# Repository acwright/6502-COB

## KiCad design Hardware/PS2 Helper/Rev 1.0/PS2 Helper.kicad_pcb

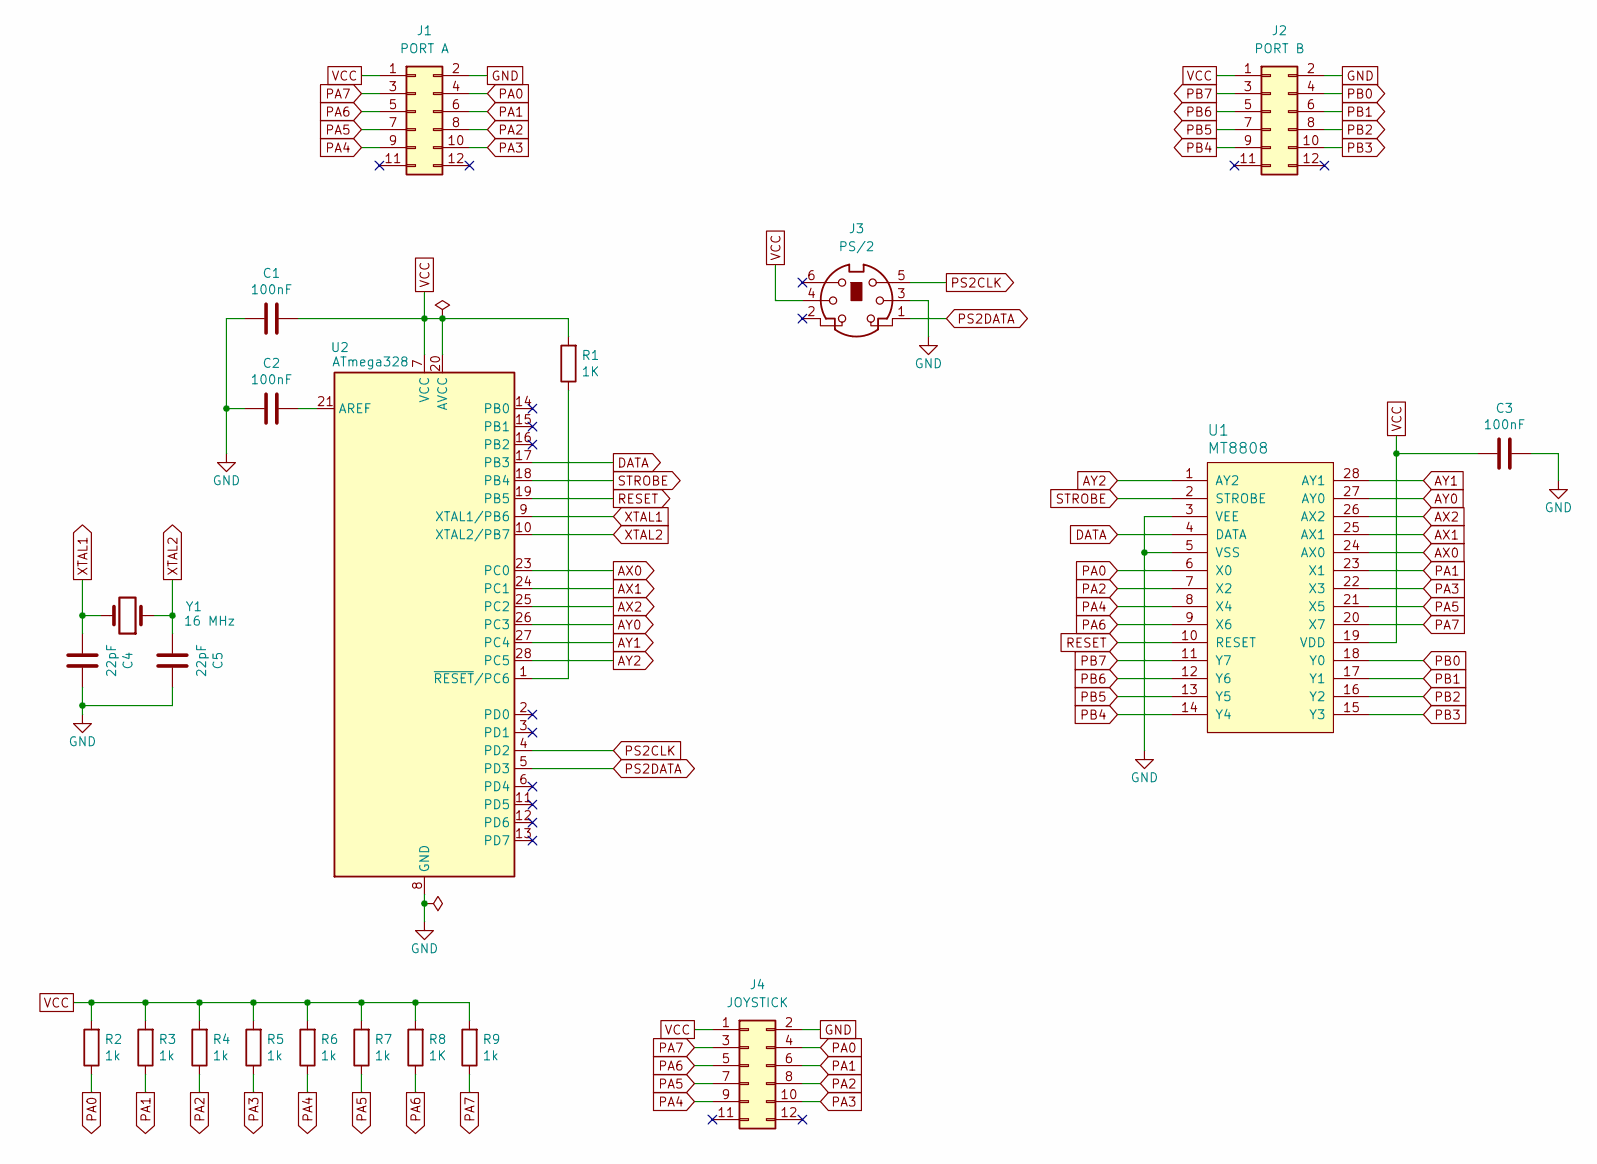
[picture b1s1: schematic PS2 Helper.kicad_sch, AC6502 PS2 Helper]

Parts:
C1, C2, C3: 100nF; C_Disc_D5.0mm_W2.5mm_P2.50mm; Digikey 478-3187-ND
C4, C5: 22pF; C_Disc_D5.0mm_W2.5mm_P2.50mm; Digikey 478-4846-ND
J1: PORT A; 6502 GPIO Connector; Digikey 2057-BHR-12-VUA-ND
J2: PORT B; 6502 GPIO Connector; Digikey 2057-BHR-12-VUA-ND
J3: PS/2; PS2 Jack; Digikey 2092-KMDGX-6S-BS-ND
J4: JOYSTICK; 6502 GPIO Connector; Digikey 2057-BHR-12-VUA-ND
R1, R8: 1K; R_Axial_DIN0204_L3.6mm_D1.6mm_P5.08mm_Horizontal; Digikey 13-MFR-12FTF52-1KCT-ND
R2, R3, R4, R5, R6, R7, R9: 1k; R_Axial_DIN0204_L3.6mm_D1.6mm_P5.08mm_Horizontal; Digikey 13-MFR-12FTF52-1KCT-ND
U1: MT8808; DIP-28_W15.24mm_Socket_LongPads
U2: ATmega328; DIP-28_W7.62mm_Socket_LongPads; Digikey ATMEGA328P-PU-ND
Y1: 16 MHz; Crystal_HC49-U_Vertical; Digikey X1103-ND

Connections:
AX0: U1.24 (AX0), U2.23 (PC0)
AX1: U1.25 (AX1), U2.24 (PC1)
AX2: U1.26 (AX2), U2.25 (PC2)
AY0: U1.27 (AY0), U2.26 (PC3)
AY1: U1.28 (AY1), U2.27 (PC4)
AY2: U1.1 (AY2), U2.28 (PC5)
DATA: U1.4 (DATA), U2.17 (PB3)
GND: C1.1, C2.1, C3.2, C4.2, C5.2, J1.2, J2.2, J3.3, J4.2, U1.3 (VEE), U1.5 (VSS), U2.8 (GND), U2.22 (GND)
unnamed: C2.2, U2.21 (AREF)
unnamed: R1.1, U2.1 (~RESET/PC6)
PA0: J1.4, J4.4, R2.1, U1.6 (X0)
PA1: J1.6, J4.6, R3.1, U1.23 (X1)
PA2: J1.8, J4.8, R4.1, U1.7 (X2)
PA3: J1.10, J4.10, R5.1, U1.22 (X3)
PA4: J1.9, J4.9, R6.1, U1.8 (X4)
PA5: J1.7, J4.7, R7.1, U1.21 (X5)
PA6: J1.5, J4.5, R8.1, U1.9 (X6)
PA7: J1.3, J4.3, R9.1, U1.20 (X7)
PB0: J2.4, U1.18 (Y0)
PB1: J2.6, U1.17 (Y1)
PB2: J2.8, U1.16 (Y2)
PB3: J2.10, U1.15 (Y3)
PB4: J2.9, U1.14 (Y4)
PB5: J2.7, U1.13 (Y5)
PB6: J2.5, U1.12 (Y6)
PB7: J2.3, U1.11 (Y7)
PS2CLK: J3.5, U2.4 (PD2)
PS2DATA: J3.1, U2.5 (PD3)
RESET: U1.10 (RESET), U2.19 (PB5)
STROBE: U1.2 (STROBE), U2.18 (PB4)
VCC: C1.2, C3.1, J1.1, J2.1, J3.4, J4.1, R1.2, R2.2, R3.2, R4.2, R5.2, R6.2, R7.2, R8.2, R9.2, U1.19 (VDD), U2.7 (VCC), U2.20 (AVCC)
XTAL1: C4.1, U2.9 (XTAL1/PB6), Y1.2
XTAL2: C5.1, U2.10 (XTAL2/PB7), Y1.1

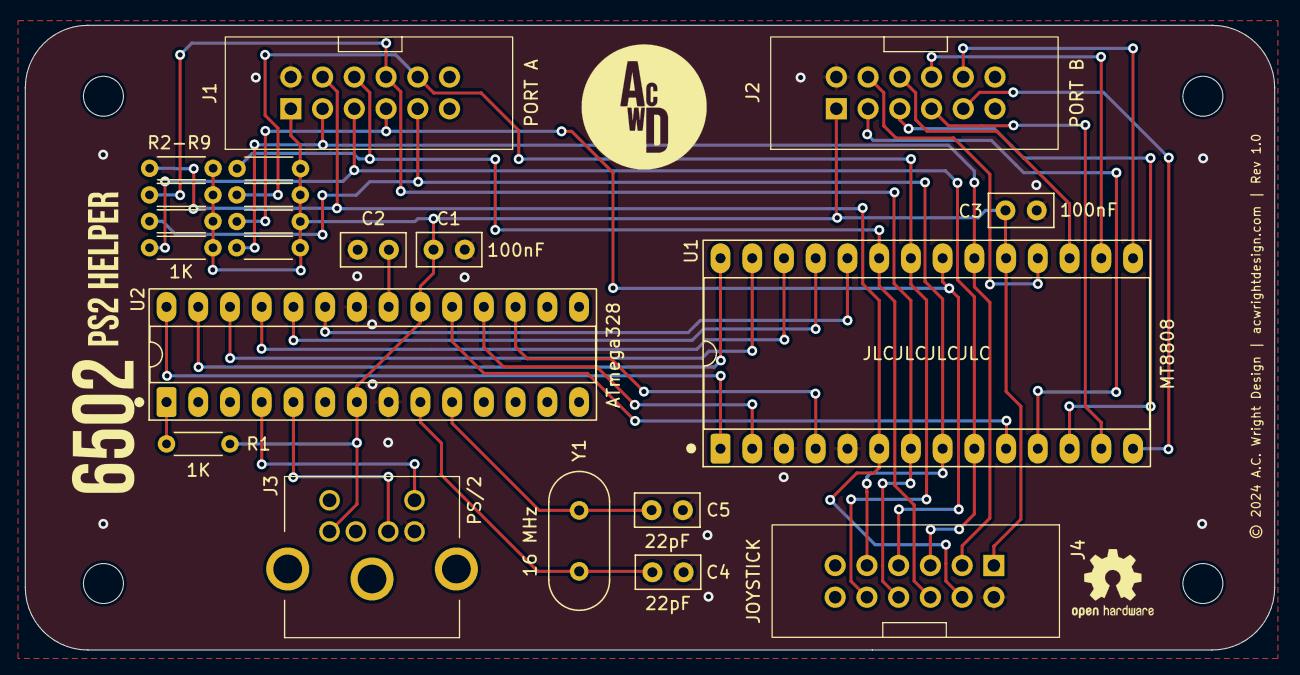
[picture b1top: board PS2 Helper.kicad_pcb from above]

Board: 2 copper layers, 100.0 x 50.0 mm, 25 parts (0 on the bottom side), 33 nets.

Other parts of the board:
H1, H2, H3, H4: MountingHole; MountingHole_3.2mm_M3

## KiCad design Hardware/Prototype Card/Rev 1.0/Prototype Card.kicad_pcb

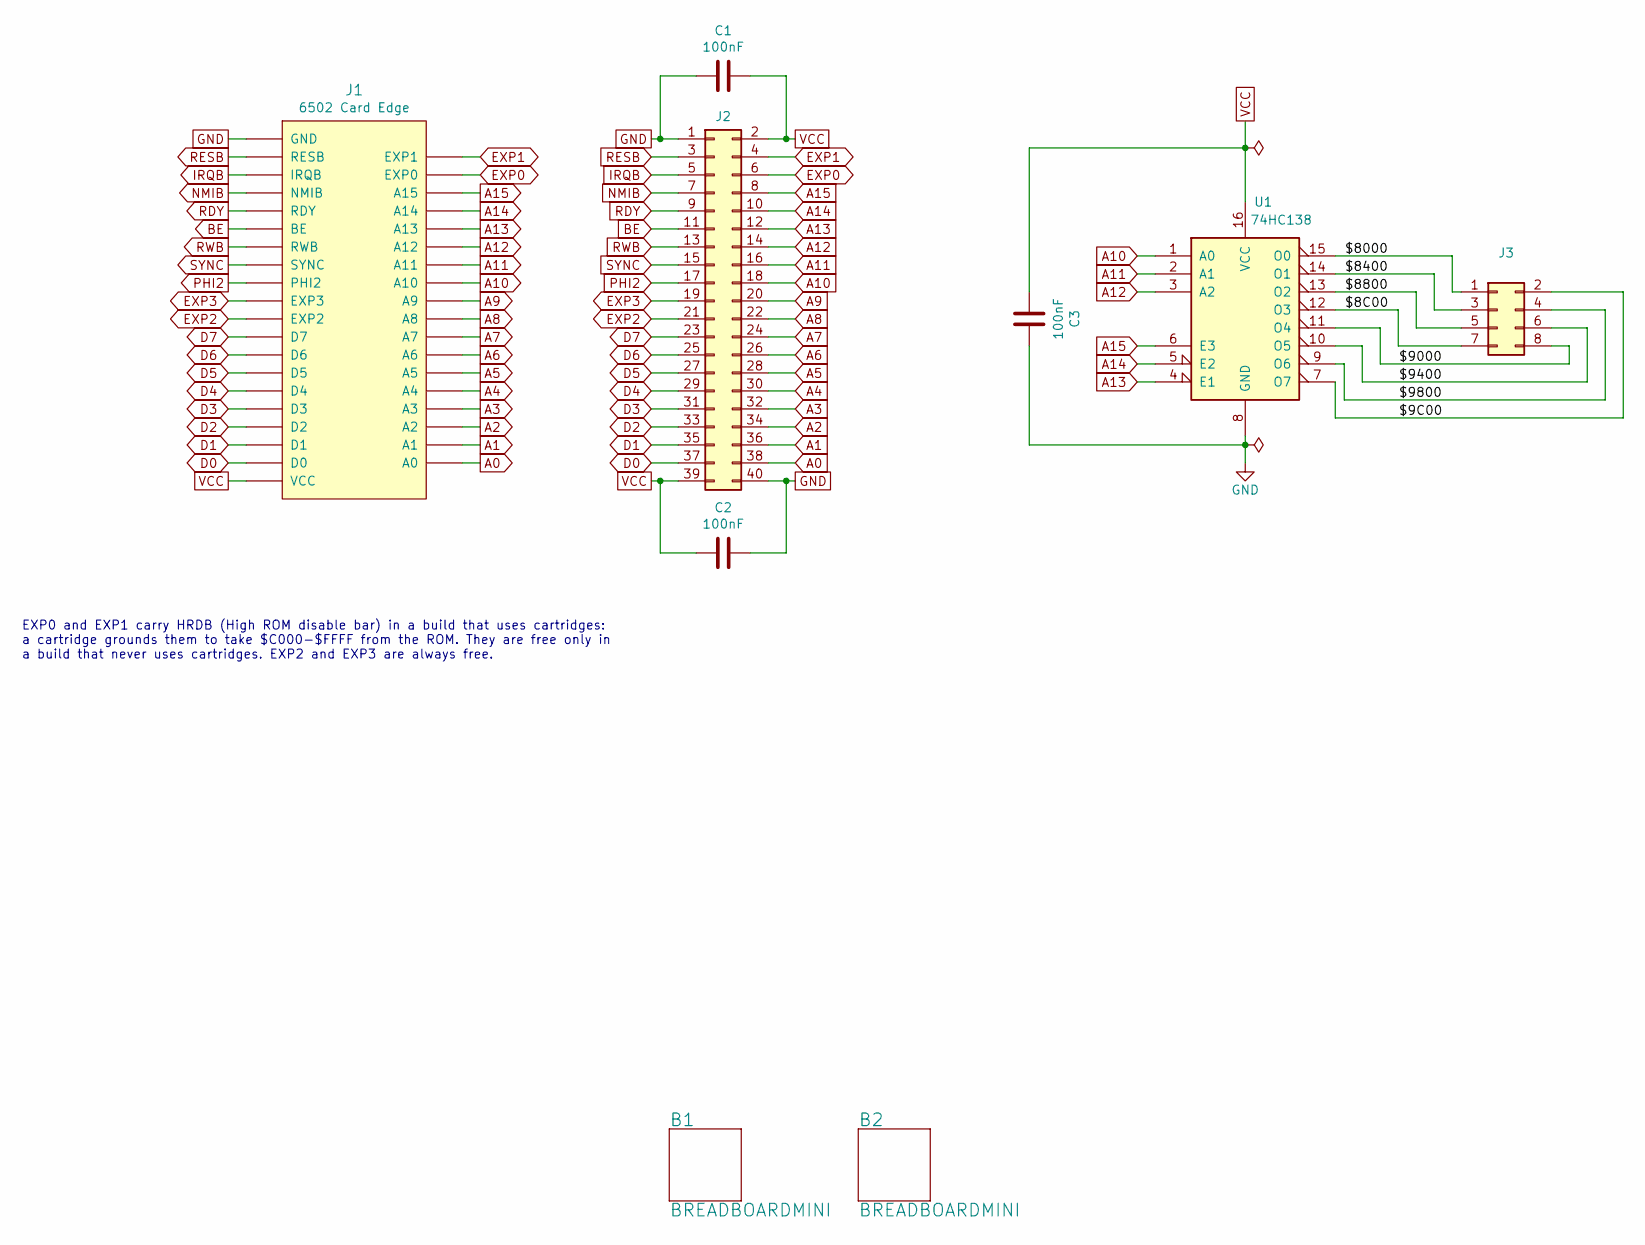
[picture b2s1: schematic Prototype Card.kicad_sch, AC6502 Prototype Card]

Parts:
B1, B2: BREADBOARDMINI; Breadboard Mini; Mouser 474-PRT-12047
C1, C2, C3: 100nF; C_0805_2012Metric; LCSC C49678
J1: 6502 Card Edge
J2: 6502 Bus; PinSocket_2x20_P2.54mm_Vertical; Digikey S7123-ND
J3: Conn_02x04_Odd_Even; PinHeader_2x04_P2.54mm_Vertical; Digikey S2011EC-40-ND
U1: 74HC138; SOIC-16_3.9x9.9mm_P1.27mm; LCSC C5602

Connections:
/$8C00: J3.7, U1.12 (O3)
/$9C00: J3.2, U1.7 (O7)
/$8000: J3.1, U1.15 (O0)
/$8400: J3.3, U1.14 (O1)
/$8800: J3.5, U1.13 (O2)
/$9000: J3.8, U1.11 (O4)
/$9400: J3.6, U1.10 (O5)
/$9800: J3.4, U1.9 (O6)
A0: J1.A0, J2.38
A1: J1.A1, J2.36
A2: J1.A2, J2.34
A3: J1.A3, J2.32
A4: J1.A4, J2.30
A5: J1.A5, J2.28
A6: J1.A6, J2.26
A7: J1.A7, J2.24
A8: J1.A8, J2.22
A9: J1.A9, J2.20
A10: J1.A10, J2.18, U1.1 (A0)
A11: J1.A11, J2.16, U1.2 (A1)
A12: J1.A12, J2.14, U1.3 (A2)
A13: J1.A13, J2.12, U1.4 (E1)
A14: J1.A14, J2.10, U1.5 (E2)
A15: J1.A15, J2.8, U1.6 (E3)
BE: J1.BE, J2.11
D0: J1.D0, J2.37
D1: J1.D1, J2.35
D2: J1.D2, J2.33
D3: J1.D3, J2.31
D4: J1.D4, J2.29
D5: J1.D5, J2.27
D6: J1.D6, J2.25
D7: J1.D7, J2.23
EXP0: J1.EXP0, J2.6
EXP1: J1.EXP1, J2.4
EXP2: J1.EXP2, J2.21
EXP3: J1.EXP3, J2.19
GND: C1.1, C2.2, C3.2, J1.GND, J2.1, J2.40, U1.8 (GND)
IRQB: J1.IRQB, J2.5
NMIB: J1.NMIB, J2.7
PHI2: J1.PHI2, J2.17
RDY: J1.RDY, J2.9
RESB: J1.RESB, J2.3
RWB: J1.RWB, J2.13
SYNC: J1.SYNC, J2.15
VCC: C1.2, C2.1, C3.1, J1.VCC, J2.2, J2.39, U1.16 (VCC)

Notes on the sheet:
EXP0 and EXP1 carry HRDB (High ROM disable bar) in a build that uses cartridges: a cartridge grounds them to take $C000-$FFFF from the ROM. They are free only in a build that never uses cartridges. EXP2 and EXP3 are always free.

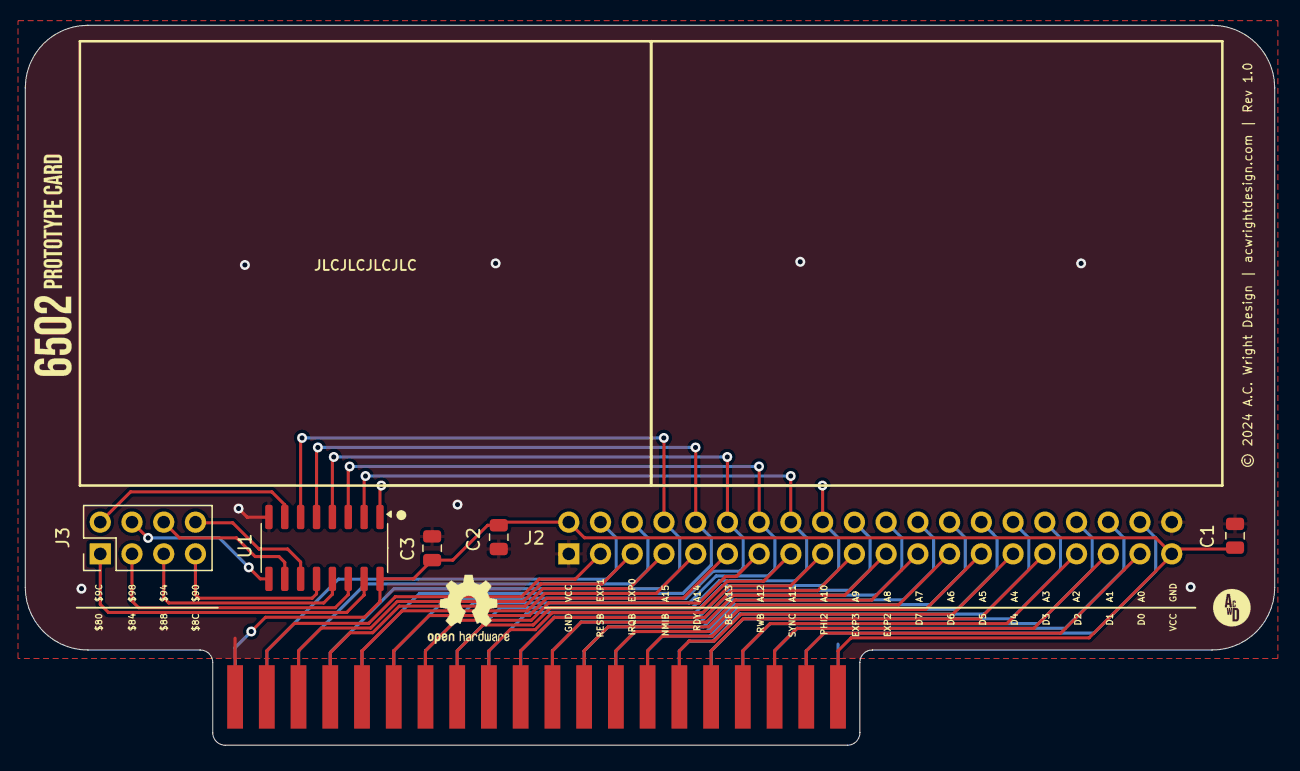
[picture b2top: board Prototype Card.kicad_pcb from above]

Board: 2 copper layers, 100.0 x 57.6 mm, 9 parts (1 on the bottom side), 46 nets.

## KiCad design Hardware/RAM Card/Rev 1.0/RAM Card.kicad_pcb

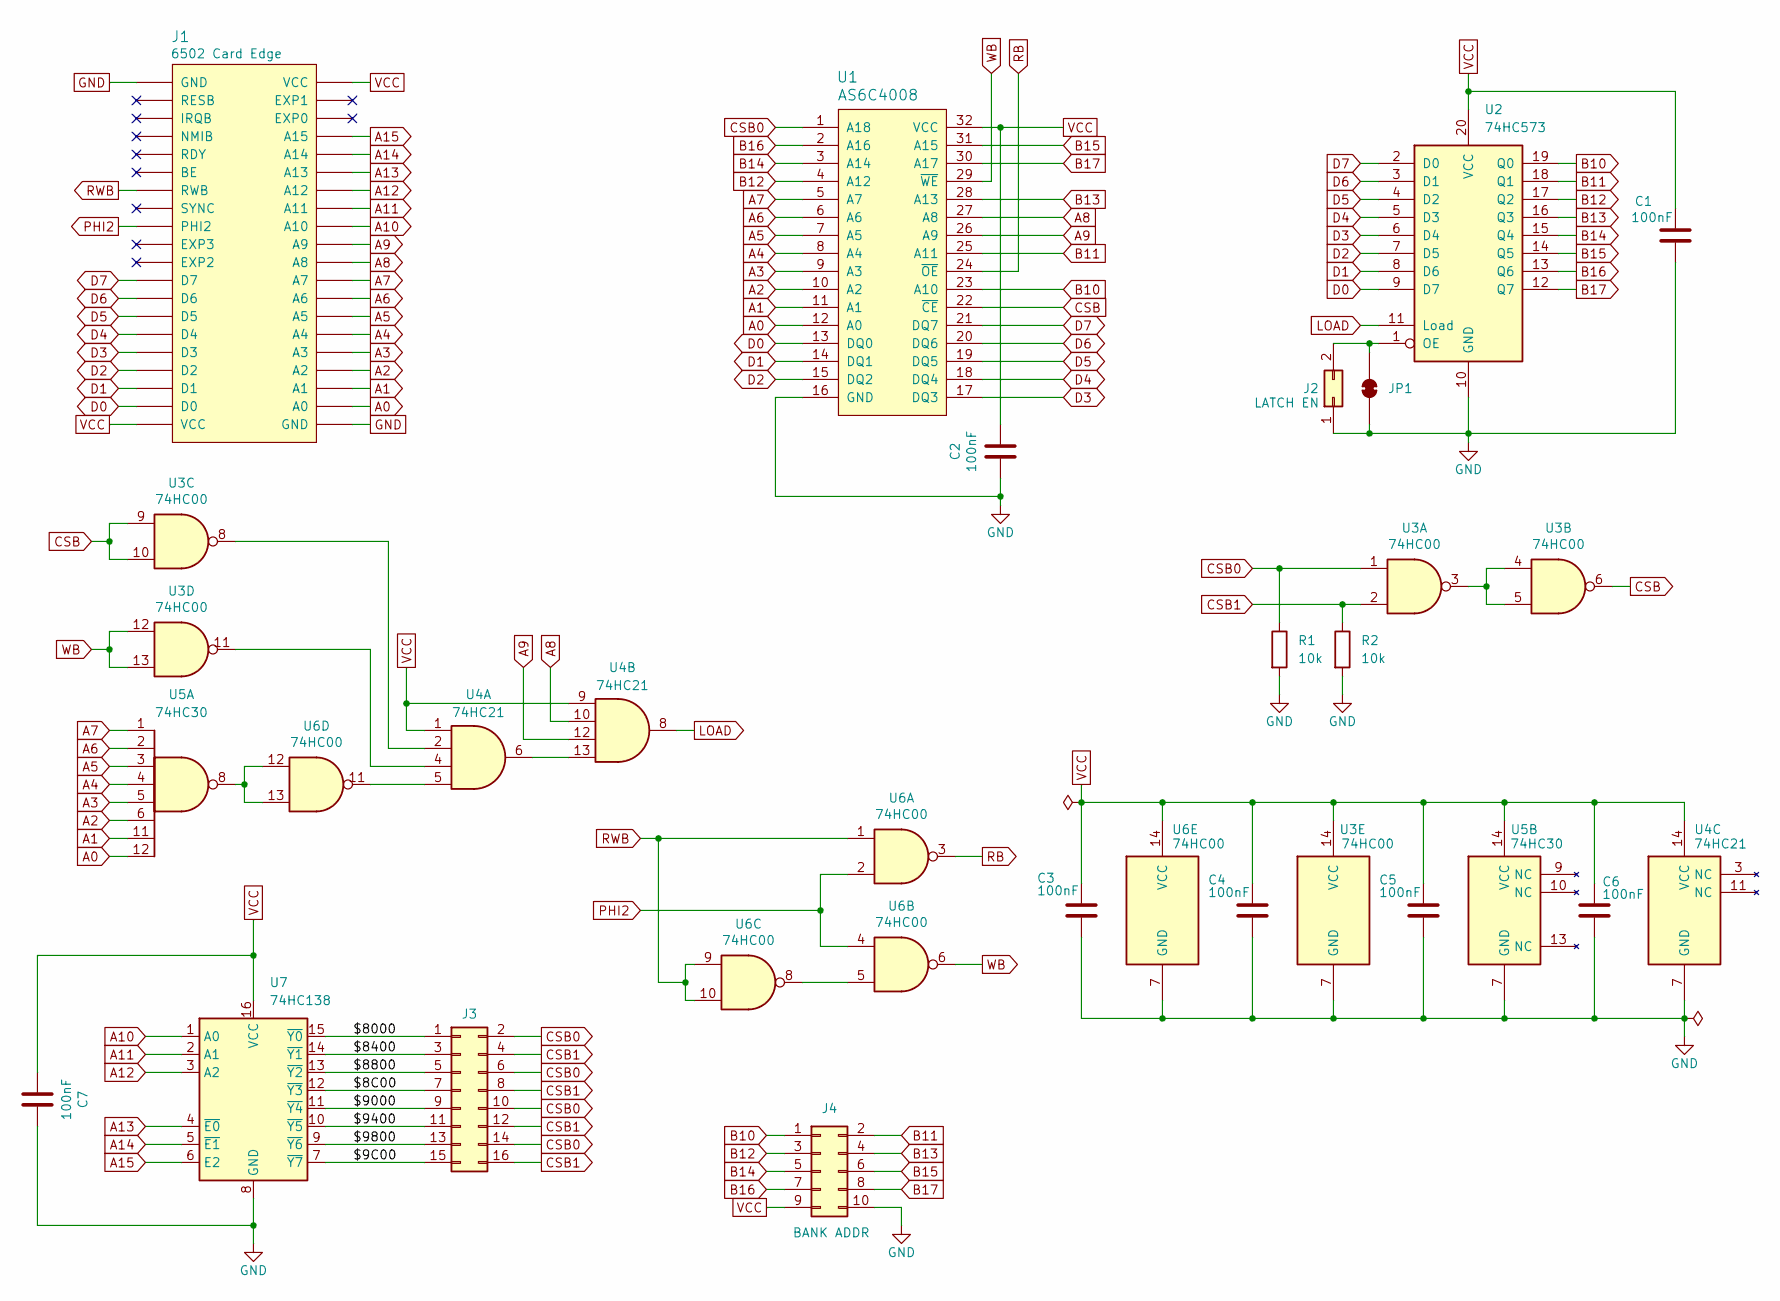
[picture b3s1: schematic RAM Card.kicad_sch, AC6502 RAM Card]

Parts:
C1, C2, C3, C4, C5, C6, C7: 100nF; C_0805_2012Metric; LCSC C49678
J1: 6502 Card Edge
J2: LATCH EN; PinHeader_1x02_P2.54mm_Vertical; Digikey S1011EC-40-ND
J3: Conn_02x08_Odd_Even; PinHeader_2x08_P2.54mm_Vertical; Digikey S2011EC-40-ND
J4: BANK ADDR; PinHeader_2x05_P2.54mm_Vertical; Digikey S2011EC-40-ND
JP1: Latch Enable; SolderJumper-2_P1.3mm_Bridged_RoundedPad1.0x1.5mm
R1, R2: 10k; R_0805_2012Metric; LCSC C17414
U1: AS6C4008; DIP-32_W15.24mm_Socket_LongPads; Digikey 1450-1027-ND
U2: 74HC573; SOIC-20W_7.5x12.8mm_P1.27mm; LCSC C5608
U3, U6: 74HC00; SOIC-14_3.9x8.7mm_P1.27mm; LCSC C5586
U4: 74HC21; SOIC-14_3.9x8.7mm_P1.27mm; LCSC C75398
U5: 74HC30; SOIC-14_3.9x8.7mm_P1.27mm; LCSC C19818870
U7: 74HC138; SOIC-16_3.9x9.9mm_P1.27mm; LCSC C5602

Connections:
/$8C00: J3.7, U7.12 (~Y3)
/$9C00: J3.15, U7.7 (~Y7)
/$8000: J3.1, U7.15 (~Y0)
/$8400: J3.3, U7.14 (~Y1)
/$8800: J3.5, U7.13 (~Y2)
/$9000: J3.9, U7.11 (~Y4)
/$9400: J3.11, U7.10 (~Y5)
/$9800: J3.13, U7.9 (~Y6)
A0: J1.A0, U1.12 (A0), U5.12
A1: J1.A1, U1.11 (A1), U5.11
A2: J1.A2, U1.10 (A2), U5.6
A3: J1.A3, U1.9 (A3), U5.5
A4: J1.A4, U1.8 (A4), U5.4
A5: J1.A5, U1.7 (A5), U5.3
A6: J1.A6, U1.6 (A6), U5.2
A7: J1.A7, U1.5 (A7), U5.1
A8: J1.A8, U1.27 (A8), U4.10
A9: J1.A9, U1.26 (A9), U4.12
A10: J1.A10, U7.1 (A0)
A11: J1.A11, U7.2 (A1)
A12: J1.A12, U7.3 (A2)
A13: J1.A13, U7.4 (~E0)
A14: J1.A14, U7.5 (~E1)
A15: J1.A15, U7.6 (E2)
B10: J4.1, U1.23 (A10), U2.19 (Q0)
B11: J4.2, U1.25 (A11), U2.18 (Q1)
B12: J4.3, U1.4 (A12), U2.17 (Q2)
B13: J4.4, U1.28 (A13), U2.16 (Q3)
B14: J4.5, U1.3 (A14), U2.15 (Q4)
B15: J4.6, U1.31 (A15), U2.14 (Q5)
B16: J4.7, U1.2 (A16), U2.13 (Q6)
B17: J4.8, U1.30 (A17), U2.12 (Q7)
CSB: U1.22 (~CE), U3.6, U3.9, U3.10
CSB0: J3.2, J3.6, J3.10, J3.14, R1.1, U1.1 (A18), U3.1
CSB1: J3.4, J3.8, J3.12, J3.16, R2.1, U3.2
D0: J1.D0, U1.13 (DQ0), U2.9 (D7)
D1: J1.D1, U1.14 (DQ1), U2.8 (D6)
D2: J1.D2, U1.15 (DQ2), U2.7 (D5)
D3: J1.D3, U1.17 (DQ3), U2.6 (D4)
D4: J1.D4, U1.18 (DQ4), U2.5 (D3)
D5: J1.D5, U1.19 (DQ5), U2.4 (D2)
D6: J1.D6, U1.20 (DQ6), U2.3 (D1)
D7: J1.D7, U1.21 (DQ7), U2.2 (D0)
GND: C1.2, C2.2, C3.2, C4.2, C5.2, C6.2, C7.2, J1.GND, J2.1, J4.10, JP1.1 (A), R1.2, R2.2, U1.16 (GND), U2.10 (GND), U3.7 (GND), U4.7 (GND), U5.7 (GND), U6.7 (GND), U7.8 (GND)
LOAD: U2.11 (Load), U4.8
unnamed: J2.2, JP1.2 (B), U2.1 (OE)
unnamed: U3.3, U3.4, U3.5
unnamed: U3.8, U4.2
unnamed: U3.11, U4.4
unnamed: U4.5, U6.11
unnamed: U4.6, U4.13
unnamed: U5.8, U6.12, U6.13
unnamed: U6.5, U6.8
PHI2: J1.PHI2, U6.2, U6.4
RB: U1.24 (~OE), U6.3
RWB: J1.RWB, U6.1, U6.9, U6.10
VCC: C1.1, C2.1, C3.1, C4.1, C5.1, C6.1, C7.1, J1.VCC, J4.9, U1.32 (VCC), U2.20 (VCC), U3.14 (VCC), U4.1, U4.9, U4.14 (VCC), U5.14 (VCC), U6.14 (VCC), U7.16 (VCC)
WB: U1.29 (~WE), U3.12, U3.13, U6.6

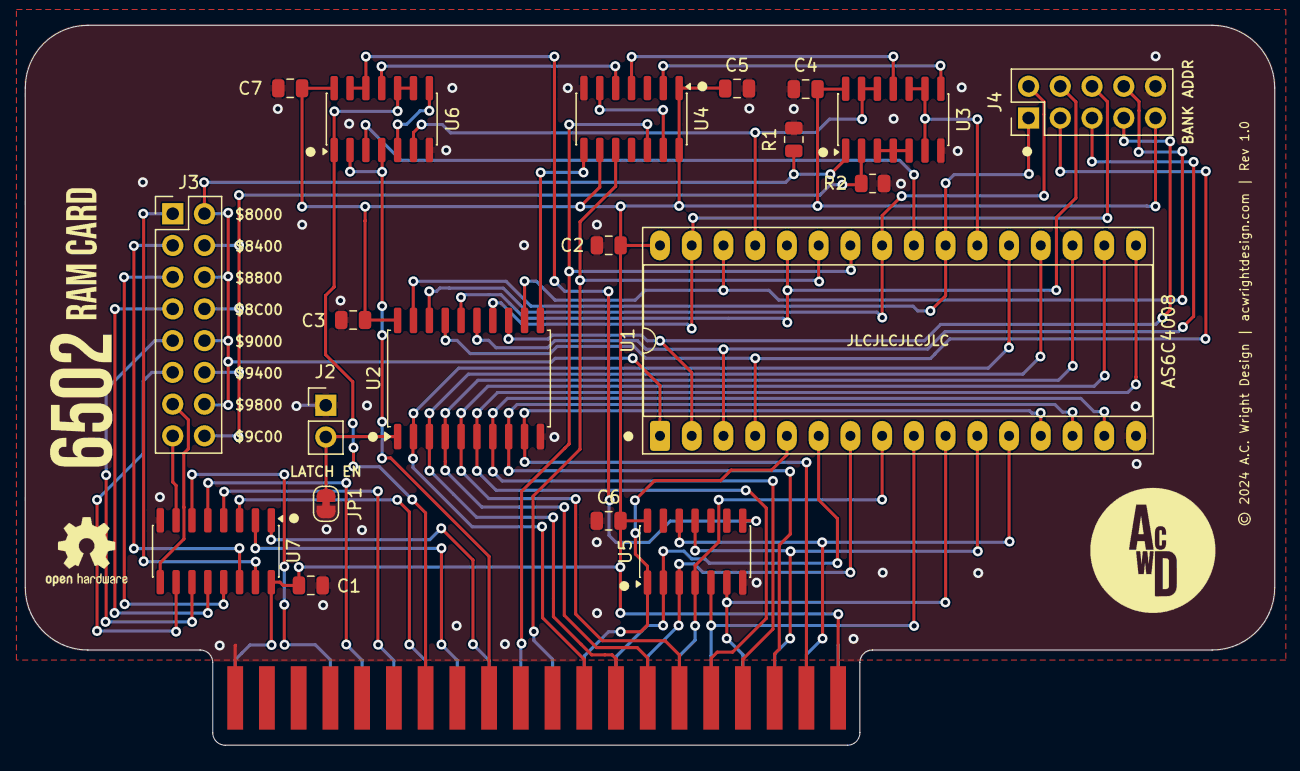
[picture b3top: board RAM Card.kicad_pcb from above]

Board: 2 copper layers, 100.0 x 57.6 mm, 21 parts (0 on the bottom side), 58 nets.

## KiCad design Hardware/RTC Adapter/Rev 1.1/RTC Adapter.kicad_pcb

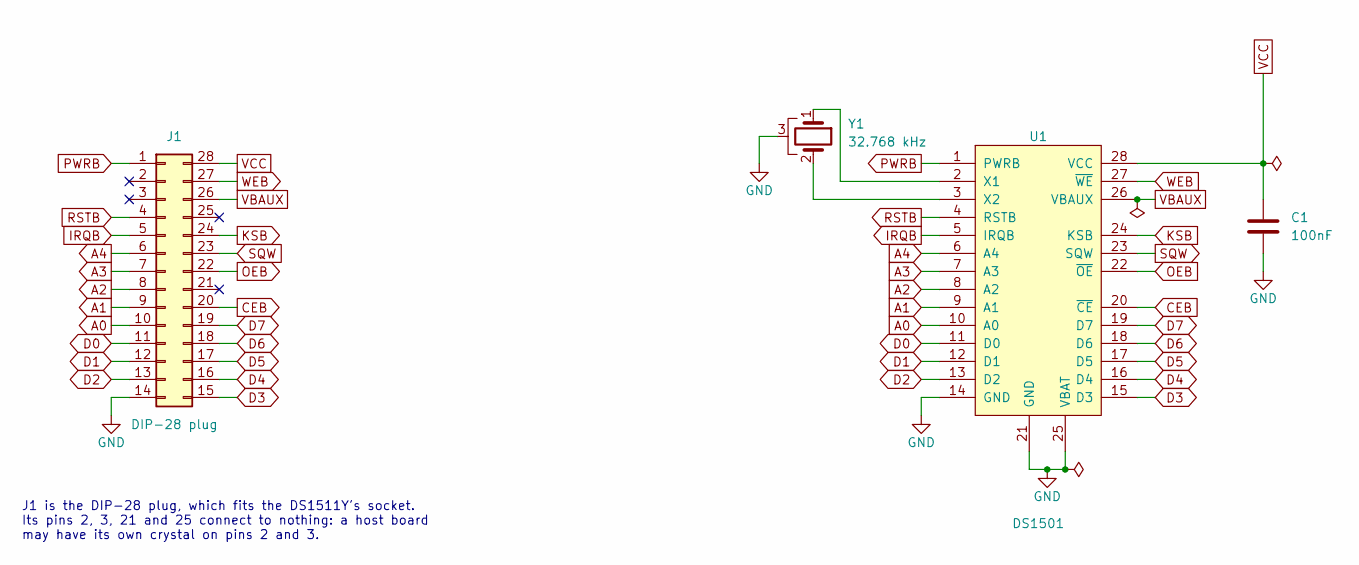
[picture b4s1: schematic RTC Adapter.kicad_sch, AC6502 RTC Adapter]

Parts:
C1: 100nF; C_Disc_D5.0mm_W2.5mm_P2.50mm; Digikey 478-3187-ND
J1: DIP-28 plug; DIP-28 Plug; Digikey ED7264-64-ND
U1: DS1501; SOIC-28W_7.5x17.9mm_P1.27mm; Digikey DS1501YZN+-ND
Y1: 32.768 kHz; Crystal_C26-LF_D2.1mm_L6.5mm_Horizontal_1EP_style1; Digikey 535-AB26T-32.768KHZ-6CT-ND

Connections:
A0: J1.10, U1.10 (A0)
A1: J1.9, U1.9 (A1)
A2: J1.8, U1.8 (A2)
A3: J1.7, U1.7 (A3)
A4: J1.6, U1.6 (A4)
CEB: J1.20, U1.20 (~CE)
D0: J1.11, U1.11 (D0)
D1: J1.12, U1.12 (D1)
D2: J1.13, U1.13 (D2)
D3: J1.15, U1.15 (D3)
D4: J1.16, U1.16 (D4)
D5: J1.17, U1.17 (D5)
D6: J1.18, U1.18 (D6)
D7: J1.19, U1.19 (D7)
GND: C1.2, J1.14, U1.14 (GND), U1.21 (GND), U1.25 (VBAT), Y1.3
IRQB: J1.5, U1.5 (IRQB)
KSB: J1.24, U1.24 (KSB)
unnamed: U1.2 (X1), Y1.1
unnamed: U1.3 (X2), Y1.2
OEB: J1.22, U1.22 (~OE)
PWRB: J1.1, U1.1 (PWRB)
RSTB: J1.4, U1.4 (RSTB)
SQW: J1.23, U1.23 (SQW)
VBAUX: J1.26, U1.26 (VBAUX)
VCC: C1.1, J1.28, U1.28 (VCC)
WEB: J1.27, U1.27 (~WE)

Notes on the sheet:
J1 is the DIP-28 plug, which fits the DS1511Y's socket. Its pins 2, 3, 21 and 25 connect to nothing: a host board may have its own crystal on pins 2 and 3.

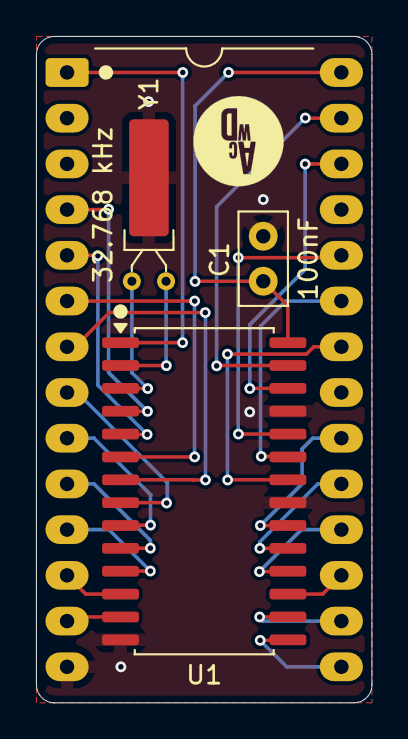
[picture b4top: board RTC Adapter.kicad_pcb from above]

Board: 2 copper layers, 18.6 x 37.0 mm, 4 parts (0 on the bottom side), 26 nets.

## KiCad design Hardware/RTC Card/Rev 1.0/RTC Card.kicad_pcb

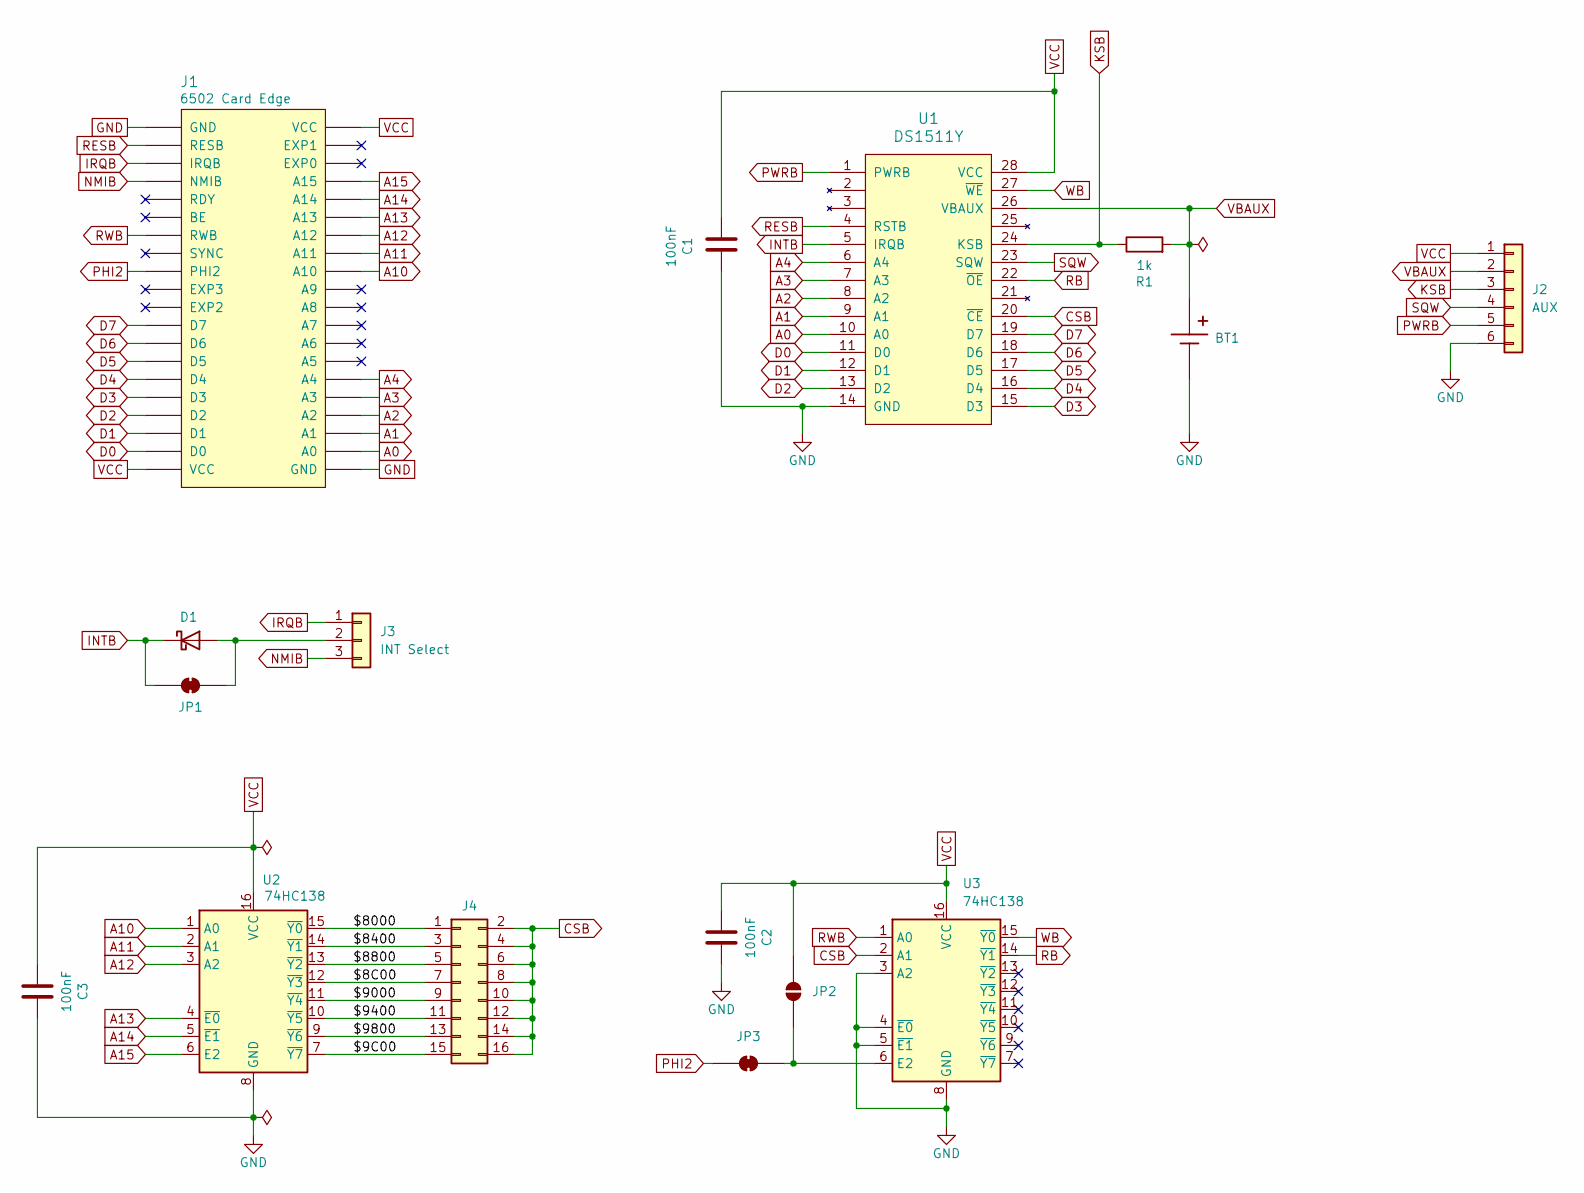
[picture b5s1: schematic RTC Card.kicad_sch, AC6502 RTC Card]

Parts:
BT1: CR2032; CR2032 Holder; Digikey 343-BAT-HLD-001-THM-TRCT-ND
C1, C2, C3: 100nF; C_0805_2012Metric; LCSC C49678
D1: BAT85; D_DO-35_SOD27_P7.62mm_Horizontal; Digikey BAT85SCT-ND
J1: 6502 Card Edge
J2: AUX; PinHeader_1x06_P2.54mm_Vertical; Digikey S1011EC-40-ND
J3: INT Select; PinHeader_1x03_P2.54mm_Vertical; Digikey S1011EC-40-ND
J4: Conn_02x08_Odd_Even; PinHeader_2x08_P2.54mm_Vertical; Digikey S2011EC-40-ND
JP1, JP3: SolderJumper_2_Bridged; SolderJumper-2_P1.3mm_Bridged_RoundedPad1.0x1.5mm
JP2: SolderJumper_2_Open; SolderJumper-2_P1.3mm_Open_RoundedPad1.0x1.5mm
R1: 1k; R_0805_2012Metric; LCSC C17513
U1: DS1511Y; DIP-28_W15.24mm_Socket_LongPads; Digikey DS1511Y+-ND
U2, U3: 74HC138; SOIC-16_3.9x9.9mm_P1.27mm; LCSC C5602

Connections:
/$8C00: J4.7, U2.12 (~Y3)
/$9C00: J4.15, U2.7 (~Y7)
/$8000: J4.1, U2.15 (~Y0)
/$8400: J4.3, U2.14 (~Y1)
/$8800: J4.5, U2.13 (~Y2)
/$9000: J4.9, U2.11 (~Y4)
/$9400: J4.11, U2.10 (~Y5)
/$9800: J4.13, U2.9 (~Y6)
A0: J1.A0, U1.10 (A0)
A1: J1.A1, U1.9 (A1)
A2: J1.A2, U1.8 (A2)
A3: J1.A3, U1.7 (A3)
A4: J1.A4, U1.6 (A4)
A10: J1.A10, U2.1 (A0)
A11: J1.A11, U2.2 (A1)
A12: J1.A12, U2.3 (A2)
A13: J1.A13, U2.4 (~E0)
A14: J1.A14, U2.5 (~E1)
A15: J1.A15, U2.6 (E2)
CSB: J4.2, J4.4, J4.6, J4.8, J4.10, J4.12, J4.14, J4.16, U1.20 (~CE), U3.2 (A1)
D0: J1.D0, U1.11 (D0)
D1: J1.D1, U1.12 (D1)
D2: J1.D2, U1.13 (D2)
D3: J1.D3, U1.15 (D3)
D4: J1.D4, U1.16 (D4)
D5: J1.D5, U1.17 (D5)
D6: J1.D6, U1.18 (D6)
D7: J1.D7, U1.19 (D7)
GND: BT1.-, C1.2, C2.2, C3.2, J1.GND, J2.6, U1.14 (GND), U2.8 (GND), U3.3 (A2), U3.4 (~E0), U3.5 (~E1), U3.8 (GND)
INTB: D1.1 (K), JP1.1 (A), U1.5 (IRQB)
IRQB: J1.IRQB, J3.1
KSB: J2.3, R1.1, U1.24 (KSB)
NMIB: J1.NMIB, J3.3
unnamed: D1.2 (A), J3.2, JP1.2 (B)
unnamed: JP2.2 (B), JP3.1 (A), U3.6 (E2)
PHI2: J1.PHI2, JP3.2 (B)
PWRB: J2.5, U1.1 (PWRB)
RB: U1.22 (~OE), U3.14 (~Y1)
RESB: J1.RESB, U1.4 (RSTB)
RWB: J1.RWB, U3.1 (A0)
SQW: J2.4, U1.23 (SQW)
VBAUX: BT1.+, J2.2, R1.2, U1.26 (VBAUX)
VCC: C1.1, C2.1, C3.1, J1.VCC, J2.1, JP2.1 (A), U1.28 (VCC), U2.16 (VCC), U3.16 (VCC)
WB: U1.27 (~WE), U3.15 (~Y0)

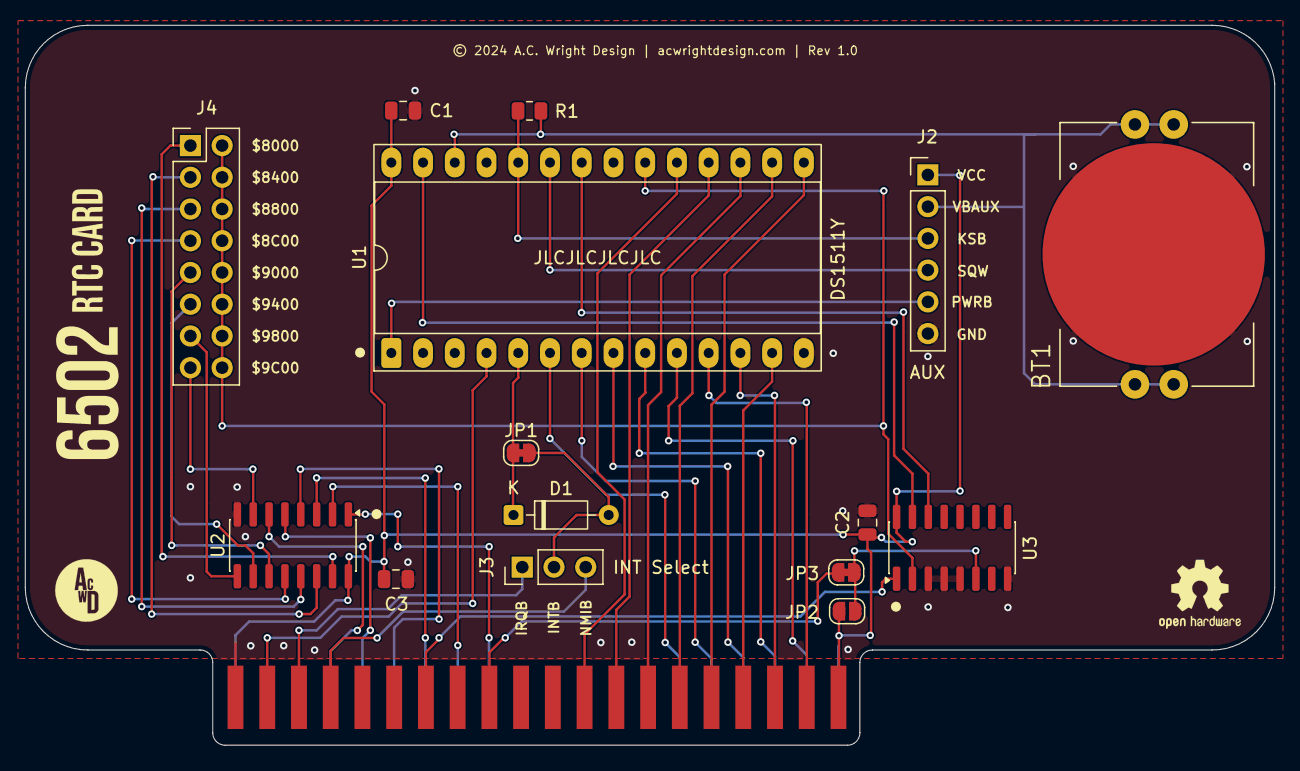
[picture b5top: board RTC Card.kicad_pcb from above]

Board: 2 copper layers, 100.0 x 57.6 mm, 16 parts (0 on the bottom side), 44 nets.

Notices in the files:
Hardware/PS2 Helper/Rev 1.0/PS2 Helper.kicad_pcb:
© 2024 A.C. Wright Design | acwrightdesign.com | Rev 1.0
Hardware/RTC Adapter/Rev 1.1/RTC Adapter.kicad_pcb:
© 2026 A.C. Wright Design | Rev 1.1
